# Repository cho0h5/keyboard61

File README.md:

# Keyboard Project

## Schematic

## PCB Layout

## 3D Rendering

## Actual Photos

### 3D Models Used
- Cherry MX Switch: [ConstantinoSchillebeeckx/cherry-mx-switch](https://github.com/ConstantinoSchillebeeckx/cherry-mx-switch)
- DSA Keycap: [anhthang/dsa-keycap](https://github.com/anhthang/dsa-keycap)

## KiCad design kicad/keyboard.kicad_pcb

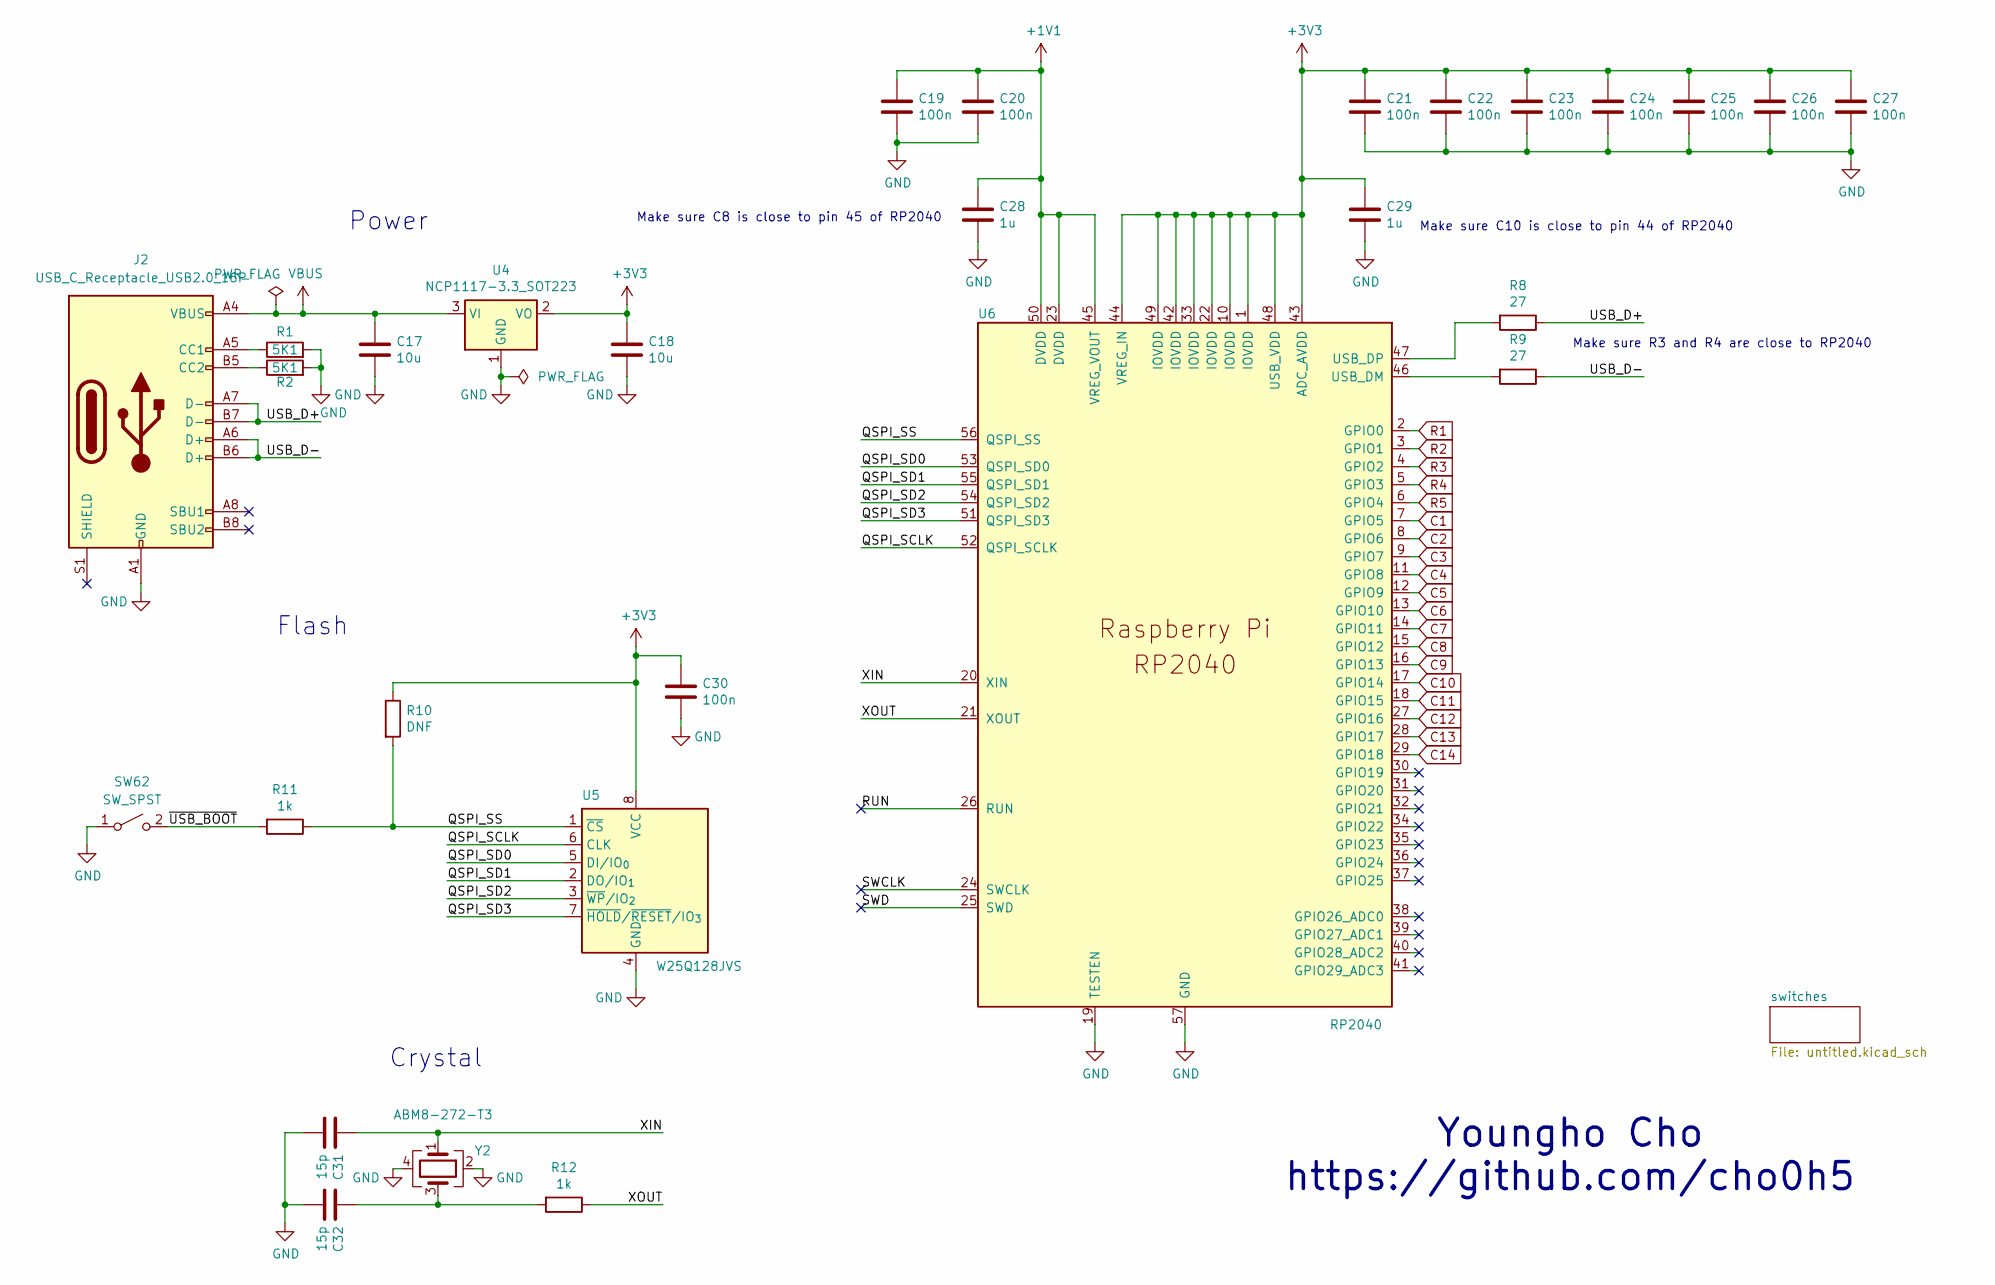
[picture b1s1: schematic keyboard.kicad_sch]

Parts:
C17, C18: 10u; C_0805_2012Metric
C19, C20, C21, C22, C23, C24, C25, C26, C27, C30: 100n; C_0402_1005Metric
C28, C29: 1u; C_0402_1005Metric
C31, C32: 15p; C_0402_1005Metric
J2: USB_C_Receptacle_USB2.0_16P; USB_C_Receptacle_GCT_USB4085
R1, R2: 5K1; R_0603_1608Metric
R8, R9: 27; R_0402_1005Metric
R10: DNF; R_0402_1005Metric
R11, R12: 1k; R_0402_1005Metric
SW62: SW_SPST; SW_SPST_SKQG_WithoutStem
U4: NCP1117-3.3_SOT223; SOT-223-3_TabPin2
U5: W25Q128JVS; SOIC-8_5.3x5.3mm_P1.27mm
U6: RP2040; RP2040-QFN-56
Y2: ABM8-272-T3; Crystal_SMD_3225-4Pin_3.2x2.5mm

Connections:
+1V1: C19.1, C20.1, C28.1, U6.23 (DVDD), U6.45 (VREG_VOUT), U6.50 (DVDD)
+3V3: C18.1, C21.1, C22.1, C23.1, C24.1, C25.1, C26.1, C27.1, C29.1, C30.1, R10.1, U4.2 (VO), U5.8 (VCC), U6.1 (IOVDD), U6.10 (IOVDD), U6.22 (IOVDD), U6.33 (IOVDD), U6.42 (IOVDD), U6.43 (ADC_AVDD), U6.44 (VREG_IN), U6.48 (USB_VDD), U6.49 (IOVDD)
/QSPI_SCLK: U5.6 (CLK), U6.52 (QSPI_SCLK)
/QSPI_SD0: U5.5 (DI/IO_{0}), U6.53 (QSPI_SD0)
/QSPI_SD1: U5.2 (DO/IO_{1}), U6.55 (QSPI_SD1)
/QSPI_SD2: U5.3 (~WP/IO_{2}), U6.54 (QSPI_SD2)
/QSPI_SD3: U5.7 (~HOLD/~RESET/IO_{3}), U6.51 (QSPI_SD3)
/QSPI_SS: R10.2, R11.1, U5.1 (~CS), U6.56 (QSPI_SS)
/RUN: U6.26 (RUN)
/SWCLK: U6.24 (SWCLK)
/SWD: U6.25 (SWD)
/USB_D+: J2.A7 (D-), J2.B7 (D-), R8.1
/USB_D-: J2.A6 (D+), J2.B6 (D+), R9.1
/XIN: C31.1, U6.20 (XIN), Y2.1
/XOUT: R12.1, U6.21 (XOUT)
/~USB_BOOT: R11.2, SW62.2 (B)
C1: U6.7 (GPIO5); also elsewhere on the board
C2: U6.8 (GPIO6); also elsewhere on the board
C3: U6.9 (GPIO7); also elsewhere on the board
C4: U6.11 (GPIO8); also elsewhere on the board
C5: U6.12 (GPIO9); also elsewhere on the board
C6: U6.13 (GPIO10); also elsewhere on the board
C7: U6.14 (GPIO11); also elsewhere on the board
C8: U6.15 (GPIO12); also elsewhere on the board
C9: U6.16 (GPIO13); also elsewhere on the board
C10: U6.17 (GPIO14); also elsewhere on the board
C11: U6.18 (GPIO15); also elsewhere on the board
C12: U6.27 (GPIO16); also elsewhere on the board
C13: U6.28 (GPIO17); also elsewhere on the board
C14: U6.29 (GPIO18); also elsewhere on the board
GND: C17.2, C18.2, C19.2, C20.2, C21.2, C22.2, C23.2, C24.2, C25.2, C26.2, C27.2, C28.2, C29.2, C30.2, C31.2, C32.2, J2.A1 (GND), J2.A12 (GND), J2.B1 (GND), J2.B12 (GND), R1.2, R2.2, SW62.1 (A), U4.1 (GND), U5.4 (GND), U6.19 (TESTEN), U6.57 (GND), Y2.2, Y2.4
unnamed: C32.1, R12.2, Y2.3
unnamed: J2.A5 (CC1), R1.1
unnamed: J2.B5 (CC2), R2.1
unnamed: R9.2, U6.46 (USB_DM)
unnamed: R8.2, U6.47 (USB_DP)
R1: U6.2 (GPIO0); also elsewhere on the board
R2: U6.3 (GPIO1); also elsewhere on the board
R3: U6.4 (GPIO2); also elsewhere on the board
R4: U6.5 (GPIO3); also elsewhere on the board
R5: U6.6 (GPIO4); also elsewhere on the board
VBUS: C17.1, J2.A4 (VBUS), J2.A9 (VBUS), J2.B4 (VBUS), J2.B9 (VBUS), U4.3 (VI)

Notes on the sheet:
Make sure C10 is close to pin 44 of RP2040
Flash
Crystal
Make sure C8 is close to pin 45 of RP2040
Make sure R3 and R4 are close to RP2040
Youngho Cho https://github.com/cho0h5
Power

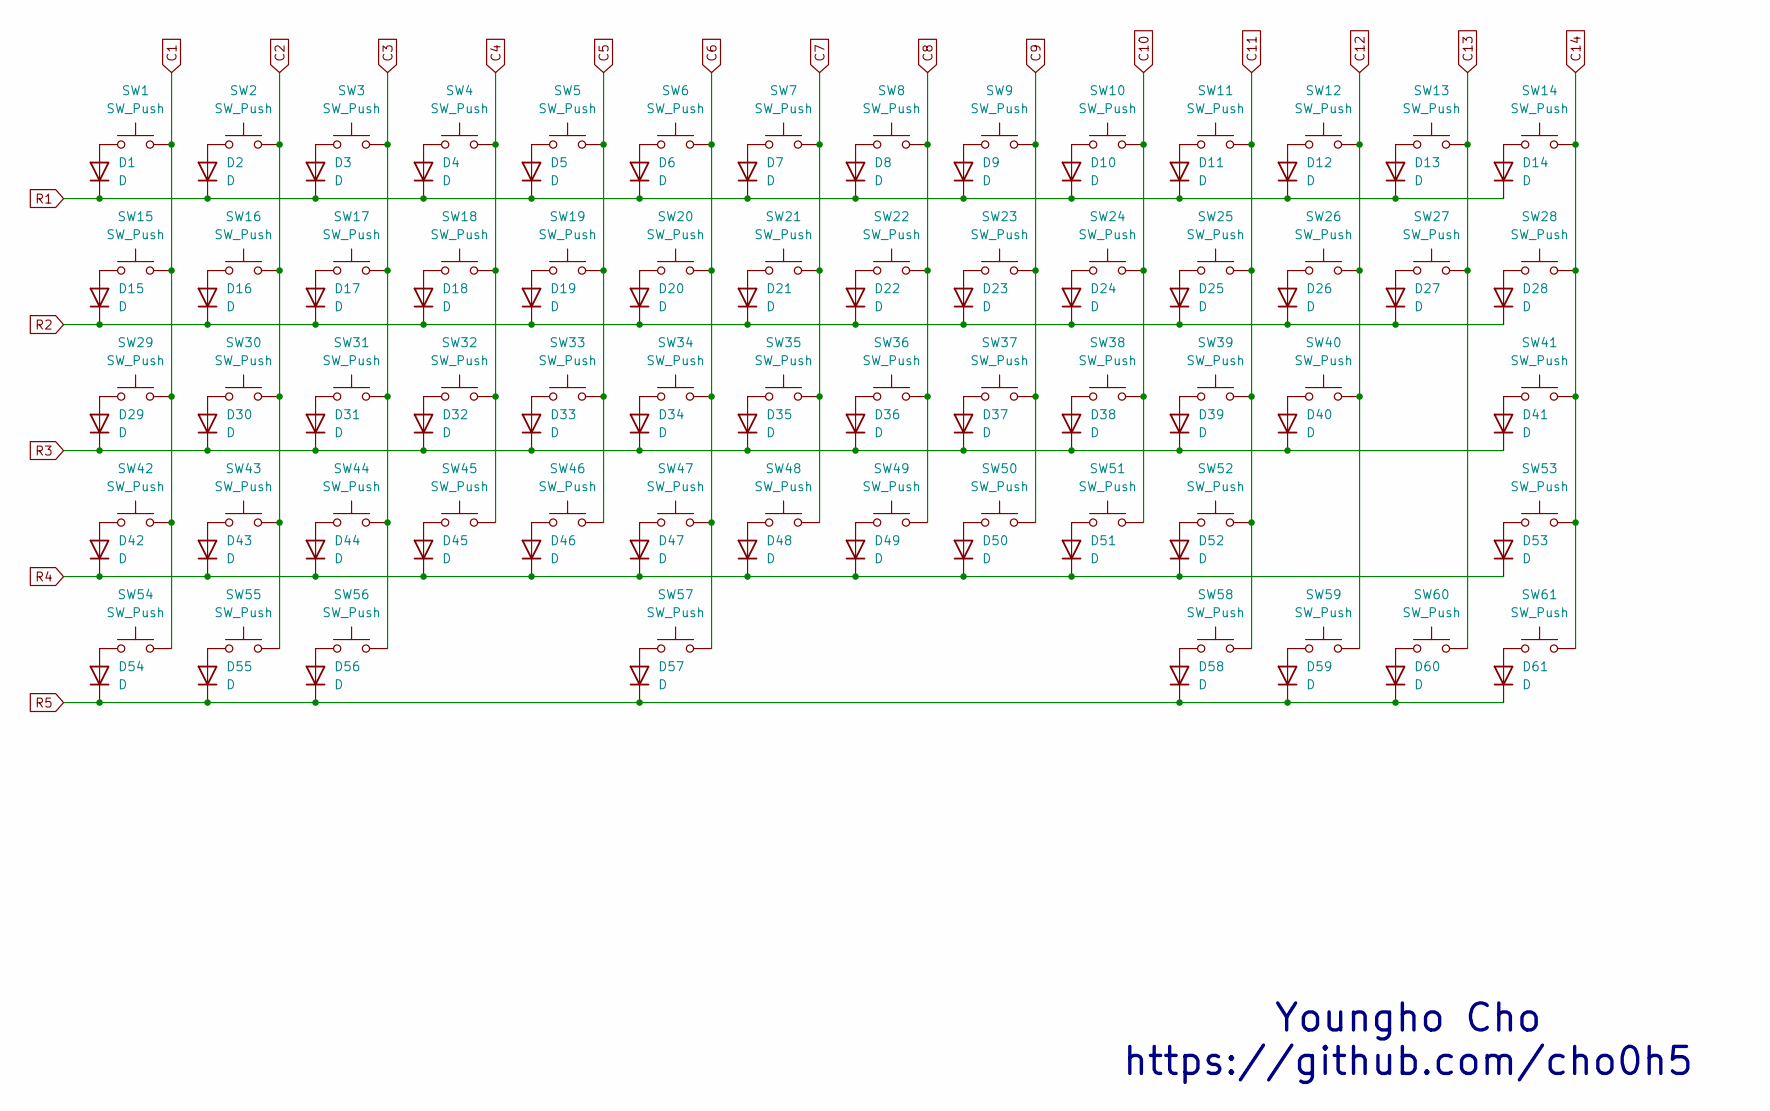
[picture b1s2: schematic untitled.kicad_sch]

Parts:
D1, D2, D3, D4, D5, D6, D7, D8, D9, D10, D11, D12, D13, D14, D15, D16, D17, D18, D19, D20, D21, D22, D23, D24, D25, D26, D27, D28, D29, D30, D31, D32, D33, D34, D35, D36, D37, D38, D39, D40, D41, D42, D43, D44, D45, D46, D47, D48, D49, D50, D51, D52, D53, D54, D55, D56, D57, D58, D59, D60, D61: D; Nexperia_CFP3_SOD-123W
SW1, SW2, SW3, SW4, SW5, SW6, SW7, SW8, SW9, SW10, SW11, SW12, SW13, SW16, SW17, SW18, SW19, SW20, SW21, SW22, SW23, SW24, SW25, SW26, SW27, SW30, SW31, SW32, SW33, SW34, SW35, SW36, SW37, SW38, SW39, SW40, SW43, SW44, SW45, SW46, SW47, SW48, SW49, SW50, SW51, SW52: SW_Push; SW_Hotswap_Kailh_MX_Plated_1.00u
SW14: SW_Push; SW_Hotswap_Kailh_MX_Plated_2.00u
SW15, SW28: SW_Push; SW_Hotswap_Kailh_MX_Plated_1.50u
SW29: SW_Push; SW_Hotswap_Kailh_MX_Plated_1.75u
SW41, SW42: SW_Push; SW_Hotswap_Kailh_MX_Plated_2.25u
SW53: SW_Push; SW_Hotswap_Kailh_MX_Plated_2.75u
SW54, SW55, SW56, SW58, SW59, SW60, SW61: SW_Push; SW_Hotswap_Kailh_MX_Plated_1.25u
SW57: SW_Push; SW_Hotswap_Kailh_MX_Plated_6.25u

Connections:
C1: SW1.2, SW15.2, SW29.2, SW42.2, SW54.2; also elsewhere on the board
C2: SW2.2, SW16.2, SW30.2, SW43.2, SW55.2; also elsewhere on the board
C3: SW3.2, SW17.2, SW31.2, SW44.2, SW56.2; also elsewhere on the board
C4: SW4.2, SW18.2, SW32.2, SW45.2; also elsewhere on the board
C5: SW5.2, SW19.2, SW33.2, SW46.2; also elsewhere on the board
C6: SW6.2, SW20.2, SW34.2, SW47.2, SW57.2; also elsewhere on the board
C7: SW7.2, SW21.2, SW35.2, SW48.2; also elsewhere on the board
C8: SW8.2, SW22.2, SW36.2, SW49.2; also elsewhere on the board
C9: SW9.2, SW23.2, SW37.2, SW50.2; also elsewhere on the board
C10: SW10.2, SW24.2, SW38.2, SW51.2; also elsewhere on the board
C11: SW11.2, SW25.2, SW39.2, SW52.2, SW58.2; also elsewhere on the board
C12: SW12.2, SW26.2, SW40.2, SW59.2; also elsewhere on the board
C13: SW13.2, SW27.2, SW60.2; also elsewhere on the board
C14: SW14.2, SW28.2, SW41.2, SW53.2, SW61.2; also elsewhere on the board
unnamed: D1.2 (A), SW1.1
unnamed: D2.2 (A), SW2.1
unnamed: D3.2 (A), SW3.1
unnamed: D4.2 (A), SW4.1
unnamed: D5.2 (A), SW5.1
unnamed: D6.2 (A), SW6.1
unnamed: D7.2 (A), SW7.1
unnamed: D8.2 (A), SW8.1
unnamed: D9.2 (A), SW9.1
unnamed: D10.2 (A), SW10.1
unnamed: D11.2 (A), SW11.1
unnamed: D12.2 (A), SW12.1
unnamed: D13.2 (A), SW13.1
unnamed: D14.2 (A), SW14.1
unnamed: D15.2 (A), SW15.1
unnamed: D16.2 (A), SW16.1
unnamed: D17.2 (A), SW17.1
unnamed: D18.2 (A), SW18.1
unnamed: D19.2 (A), SW19.1
unnamed: D20.2 (A), SW20.1
unnamed: D21.2 (A), SW21.1
unnamed: D22.2 (A), SW22.1
unnamed: D23.2 (A), SW23.1
unnamed: D24.2 (A), SW24.1
unnamed: D25.2 (A), SW25.1
unnamed: D26.2 (A), SW26.1
unnamed: D27.2 (A), SW27.1
unnamed: D28.2 (A), SW28.1
unnamed: D29.2 (A), SW29.1
unnamed: D30.2 (A), SW30.1
unnamed: D31.2 (A), SW31.1
unnamed: D32.2 (A), SW32.1
unnamed: D33.2 (A), SW33.1
unnamed: D34.2 (A), SW34.1
unnamed: D35.2 (A), SW35.1
unnamed: D36.2 (A), SW36.1
unnamed: D37.2 (A), SW37.1
unnamed: D38.2 (A), SW38.1
unnamed: D39.2 (A), SW39.1
unnamed: D40.2 (A), SW40.1
unnamed: D41.2 (A), SW41.1
unnamed: D42.2 (A), SW42.1
unnamed: D43.2 (A), SW43.1
unnamed: D44.2 (A), SW44.1
unnamed: D45.2 (A), SW45.1
unnamed: D46.2 (A), SW46.1
unnamed: D47.2 (A), SW47.1
unnamed: D48.2 (A), SW48.1
unnamed: D49.2 (A), SW49.1
unnamed: D50.2 (A), SW50.1
unnamed: D51.2 (A), SW51.1
unnamed: D52.2 (A), SW52.1
unnamed: D53.2 (A), SW53.1
unnamed: D54.2 (A), SW54.1
unnamed: D55.2 (A), SW55.1
unnamed: D56.2 (A), SW56.1
unnamed: D57.2 (A), SW57.1
unnamed: D58.2 (A), SW58.1
unnamed: D59.2 (A), SW59.1
unnamed: D60.2 (A), SW60.1
unnamed: D61.2 (A), SW61.1
R1: D1.1 (K), D2.1 (K), D3.1 (K), D4.1 (K), D5.1 (K), D6.1 (K), D7.1 (K), D8.1 (K), D9.1 (K), D10.1 (K), D11.1 (K), D12.1 (K), D13.1 (K), D14.1 (K); also elsewhere on the board
R2: D15.1 (K), D16.1 (K), D17.1 (K), D18.1 (K), D19.1 (K), D20.1 (K), D21.1 (K), D22.1 (K), D23.1 (K), D24.1 (K), D25.1 (K), D26.1 (K), D27.1 (K), D28.1 (K); also elsewhere on the board
R3: D29.1 (K), D30.1 (K), D31.1 (K), D32.1 (K), D33.1 (K), D34.1 (K), D35.1 (K), D36.1 (K), D37.1 (K), D38.1 (K), D39.1 (K), D40.1 (K), D41.1 (K); also elsewhere on the board
R4: D42.1 (K), D43.1 (K), D44.1 (K), D45.1 (K), D46.1 (K), D47.1 (K), D48.1 (K), D49.1 (K), D50.1 (K), D51.1 (K), D52.1 (K), D53.1 (K); also elsewhere on the board
R5: D54.1 (K), D55.1 (K), D56.1 (K), D57.1 (K), D58.1 (K), D59.1 (K), D60.1 (K), D61.1 (K); also elsewhere on the board

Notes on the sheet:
Youngho Cho https://github.com/cho0h5

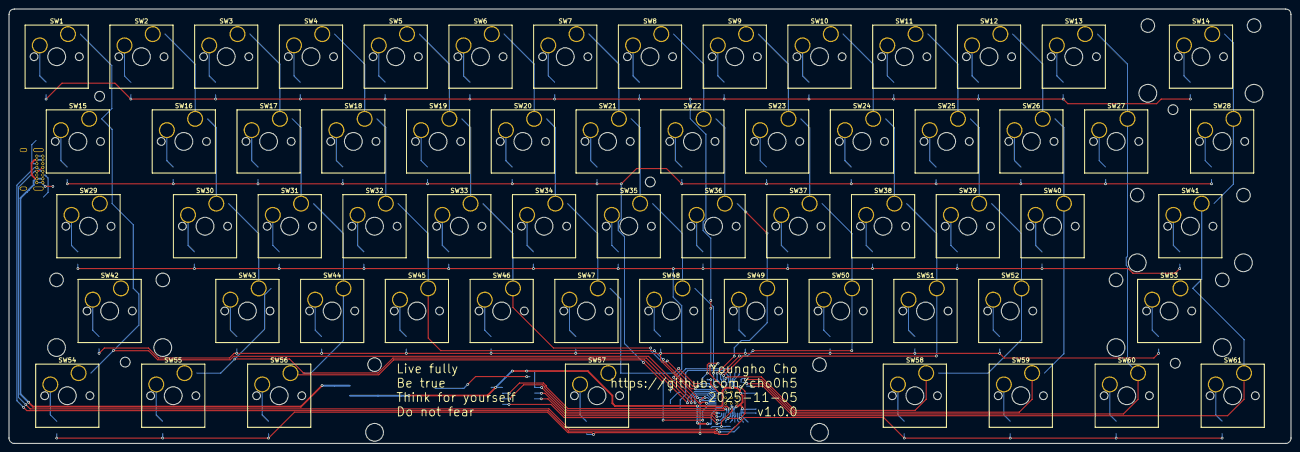
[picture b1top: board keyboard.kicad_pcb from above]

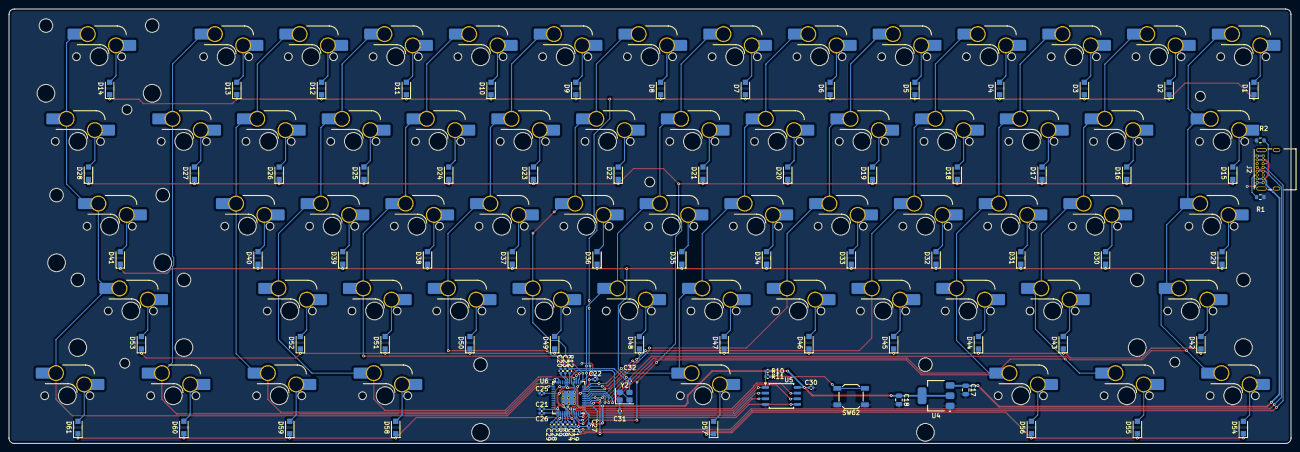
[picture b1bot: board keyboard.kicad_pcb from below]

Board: 2 copper layers, 288.1 x 97.6 mm, 151 parts (90 on the bottom side), 100 nets.

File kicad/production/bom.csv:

Designator,Footprint,Quantity,Value,LCSC Part #
"C17, C18",0805,2,10u,
"C19, C20, C21, C22, C23, C24, C25, C26, C27, C30",0402,10,100n,
"C28, C29",0402,2,1u,
"C31, C32",0402,2,15p,
"D1, D10, D11, D12, D13, D14, D15, D16, D17, D18, D19, D2, D20, D21, D22, D23, D24, D25, D26, D27, D28, D29, D3, D30, D31, D32, D33, D34, D35, D36, D37, D38, D39, D4, D40, D41, D42, D43, D44, D45, D46, D47, D48, D49, D5, D50, D51, D52, D53, D54, D55, D56, D57, D58, D59, D6, D60, D61, D7, D8, D9",Nexperia_CFP3_SOD-123W,61,D,
J2,USB_C_Receptacle_GCT_USB4085,1,USB_C_Receptacle_USB2.0_16P,
"R1, R2",0603,2,5K1,
R10,0402,1,DNF,
"R11, R12",0402,2,1k,
"R8, R9",0402,2,27,
"SW1, SW10, SW11, SW12, SW13, SW16, SW17, SW18, SW19, SW2, SW20, SW21, SW22, SW23, SW24, SW25, SW26, SW27, SW3, SW30, SW31, SW32, SW33, SW34, SW35, SW36, SW37, SW38, SW39, SW4, SW40, SW43, SW44, SW45, SW46, SW47, SW48, SW49, SW5, SW50, SW51, SW52, SW6, SW7, SW8, SW9",SW_Hotswap_Kailh_MX_Plated_1.00u,46,SW_Push,
SW14,SW_Hotswap_Kailh_MX_Plated_2.00u,1,SW_Push,
"SW15, SW28",SW_Hotswap_Kailh_MX_Plated_1.50u,2,SW_Push,
SW29,SW_Hotswap_Kailh_MX_Plated_1.75u,1,SW_Push,
"SW41, SW42",SW_Hotswap_Kailh_MX_Plated_2.25u,2,SW_Push,
SW53,SW_Hotswap_Kailh_MX_Plated_2.75u,1,SW_Push,
"SW54, SW55, SW56, SW58, SW59, SW60, SW61",SW_Hotswap_Kailh_MX_Plated_1.25u,7,SW_Push,
SW57,SW_Hotswap_Kailh_MX_Plated_6.25u,1,SW_Push,
SW62,SW_SPST_SKQG_WithoutStem,1,SW_SPST,
U4,SOT-223-3_TabPin2,1,NCP1117-3.3_SOT223,
U5,SOIC-8_5.3x5.3mm_P1.27mm,1,W25Q128JVS,
U6,RP2040-QFN-56,1,RP2040,
Y2,Crystal_SMD_3225-4Pin_3.2x2.5mm,1,ABM8-272-T3,

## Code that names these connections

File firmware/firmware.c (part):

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#define NUM_ROWS 5
#define NUM_COLS 14

// Row pins: GPIO0-4 (connected to R1-R5 via pins 2-6)
#define ROW1_PIN 0  // GPIO0 -> Pin 2 -> R1
#define ROW2_PIN 1  // GPIO1 -> Pin 3 -> R2
#define ROW3_PIN 2  // GPIO2 -> Pin 4 -> R3
#define ROW4_PIN 3  // GPIO3 -> Pin 5 -> R4
#define ROW5_PIN 4  // GPIO4 -> Pin 6 -> R5

// Column pins: GPIO5-18 (connected to C1-C14)
#define COL1_PIN  5   // GPIO5  -> Pin 7  -> C1
#define COL2_PIN  6   // GPIO6  -> Pin 8  -> C2
#define COL3_PIN  7   // GPIO7  -> Pin 9  -> C3
#define COL4_PIN  8   // GPIO8  -> Pin 11 -> C4
#define COL5_PIN  9   // GPIO9  -> Pin 12 -> C5
#define COL6_PIN  10  // GPIO10 -> Pin 13 -> C6
#define COL7_PIN  11  // GPIO11 -> Pin 14 -> C7
#define COL8_PIN  12  // GPIO12 -> Pin 15 -> C8
#define COL9_PIN  13  // GPIO13 -> Pin 16 -> C9
#define COL10_PIN 14  // GPIO14 -> Pin 17 -> C10
#define COL11_PIN 15  // GPIO15 -> Pin 18 -> C11
#define COL12_PIN 16  // GPIO16 -> Pin 27 -> C12
#define COL13_PIN 17  // GPIO17 -> Pin 28 -> C13
#define COL14_PIN 18  // GPIO18 -> Pin 29 -> C14

// Pin arrays
const uint8_t row_pins[NUM_ROWS] = {ROW1_PIN, ROW2_PIN, ROW3_PIN, ROW4_PIN, ROW5_PIN};
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#define MAX_MATRIX_KEYS (NUM_ROWS * NUM_COLS)

// Keymap: [row][col] - Standard 60% keyboard layout
// Columns: C1(GPIO5), C2(GPIO6), C3(GPIO7), C4(GPIO8), C5(GPIO9), C6(GPIO10), C7(GPIO11), C8(GPIO12), C9(GPIO13), C10(GPIO14), C11(GPIO15), C12(GPIO16), C13(GPIO17), C14(GPIO18)
const uint8_t keymap[NUM_ROWS][NUM_COLS] = {
    // Row 1 (R1 - GPIO0): Number row
    {HID_KEY_GRAVE, HID_KEY_1, HID_KEY_2, HID_KEY_3, HID_KEY_4, HID_KEY_5, HID_KEY_6, HID_KEY_7, HID_KEY_8, HID_KEY_9, HID_KEY_0, HID_KEY_MINUS, HID_KEY_EQUAL, HID_KEY_BACKSPACE},

    // Row 2 (R2 - GPIO1): Top letter row
    {HID_KEY_TAB, HID_KEY_Q, HID_KEY_W, HID_KEY_E, HID_KEY_R, HID_KEY_T, HID_KEY_Y, HID_KEY_U, HID_KEY_I, HID_KEY_O, HID_KEY_P, HID_KEY_BRACKET_LEFT, HID_KEY_BRACKET_RIGHT, HID_KEY_BACKSLASH},

    // Row 3 (R3 - GPIO2): Home row
    {HID_KEY_CONTROL_LEFT, HID_KEY_A, HID_KEY_S, HID_KEY_D, HID_KEY_F, HID_KEY_G, HID_KEY_H, HID_KEY_J, HID_KEY_K, HID_KEY_L, HID_KEY_SEMICOLON, HID_KEY_APOSTROPHE, HID_KEY_NONE, HID_KEY_ENTER},

    // Row 4 (R4 - GPIO3): Bottom letter row
    {HID_KEY_SHIFT_LEFT, HID_KEY_Z, HID_KEY_X, HID_KEY_C, HID_KEY_V, HID_KEY_B, HID_KEY_N, HID_KEY_M, HID_KEY_COMMA, HID_KEY_PERIOD, HID_KEY_SLASH, HID_KEY_NONE, HID_KEY_NONE, HID_KEY_SHIFT_RIGHT},

    // Row 5 (R5 - GPIO4): Bottom modifier row
    {HID_KEY_FN, HID_KEY_GUI_LEFT, HID_KEY_ALT_LEFT, HID_KEY_NONE, HID_KEY_NONE, HID_KEY_SPACE, HID_KEY_NONE, HID_KEY_NONE, HID_KEY_NONE, HID_KEY_NONE, HID_KEY_ARROW_LEFT, HID_KEY_ARROW_DOWN, HID_KEY_ARROW_UP, HID_KEY_ARROW_RIGHT}
};

// FN Layer: When FN key is pressed
const uint8_t fn_keymap[NUM_ROWS][NUM_COLS] = {
    // Row 1 (R1 - GPIO0): Function keys
    {HID_KEY_ESCAPE, HID_KEY_F1, HID_KEY_F2, HID_KEY_F3, HID_KEY_F4, HID_KEY_F5, HID_KEY_F6, HID_KEY_F7, HID_KEY_F8, HID_KEY_F9, HID_KEY_F10, HID_KEY_F11, HID_KEY_F12, HID_KEY_DELETE},

    // Row 2 (R2 - GPIO1): Top letter row
    {HID_KEY_TAB, HID_KEY_Q, HID_KEY_W, HID_KEY_E, HID_KEY_R, HID_KEY_T, HID_KEY_Y, HID_KEY_U, HID_KEY_I, HID_KEY_O, HID_KEY_P, HID_KEY_BRACKET_LEFT, HID_KEY_BRACKET_RIGHT, HID_KEY_BACKSLASH},

    // Row 3 (R3 - GPIO2): Home row
    {HID_KEY_CONTROL_LEFT, HID_KEY_A, HID_KEY_S, HID_KEY_D, HID_KEY_F, HID_KEY_G, HID_KEY_H, HID_KEY_J, HID_KEY_K, HID_KEY_L, HID_KEY_SEMICOLON, HID_KEY_APOSTROPHE, HID_KEY_NONE, HID_KEY_ENTER},

    // Row 4 (R4 - GPIO3): Bottom letter row
    {HID_KEY_SHIFT_LEFT, HID_KEY_Z, HID_KEY_X, HID_KEY_C, HID_KEY_V, HID_KEY_B, HID_KEY_N, HID_KEY_M, HID_KEY_COMMA, HID_KEY_PERIOD, HID_KEY_SLASH, HID_KEY_NONE, HID_KEY_NONE, HID_KEY_SHIFT_RIGHT},

    // Row 5 (R5 - GPIO4): Bottom modifier row
    {HID_KEY_FN, HID_KEY_GUI_LEFT, HID_KEY_ALT_LEFT, HID_KEY_NONE, HID_KEY_NONE, HID_KEY_SPACE, HID_KEY_NONE, HID_KEY_NONE, HID_KEY_NONE, HID_KEY_NONE, HID_KEY_ARROW_LEFT, HID_KEY_ARROW_DOWN, HID_KEY_ARROW_UP, HID_KEY_ARROW_RIGHT}
};

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
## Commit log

2025-11-05 feat: design pcb
2025-11-05 docs: add schematic svg
2025-11-05 chore: resize pcb paper
2025-11-05 chore: gitignore
2025-11-05 docs: add pcb.png
2025-11-05 chore: backup files
2025-11-05 docs: add README.md
2025-11-05 docs: change svg to png
2025-11-05 feat: add track and cut line to step
2025-11-08 docs: add rendering image
2025-11-09 docs: udpate rendering images
2025-11-09 docs: add ref for models
2025-11-09 chore: remove backupfiles
2025-11-10 feat: add gerbers
2025-11-11 feat: add fusion and stl
2025-11-15 fix: shallow wall in case
2025-11-15 feat: init pico firmware
2025-11-16 feat: add tusb boilerplate
2025-11-16 test
2025-11-16 feat: blink led when z pressed
2025-11-16 fix: hid report format
2025-11-16 feat: make switch as z key
2025-11-16 feat: change z to a key
2025-11-16 feat: 2x2 matrix keyboard
2025-11-21 feat: add actual photos
2025-11-21 feat: impl all keys
2025-11-22 feat: multiple key input
2025-12-01 feat: add hole for bootsel btn
2025-12-04 add: bootloader and GUI
2025-12-12 fix: stop firmware while update
